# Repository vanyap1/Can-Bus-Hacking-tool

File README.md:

# Can bus tools

For this moment the tool is not ready to use. 
This is only old first draft version.

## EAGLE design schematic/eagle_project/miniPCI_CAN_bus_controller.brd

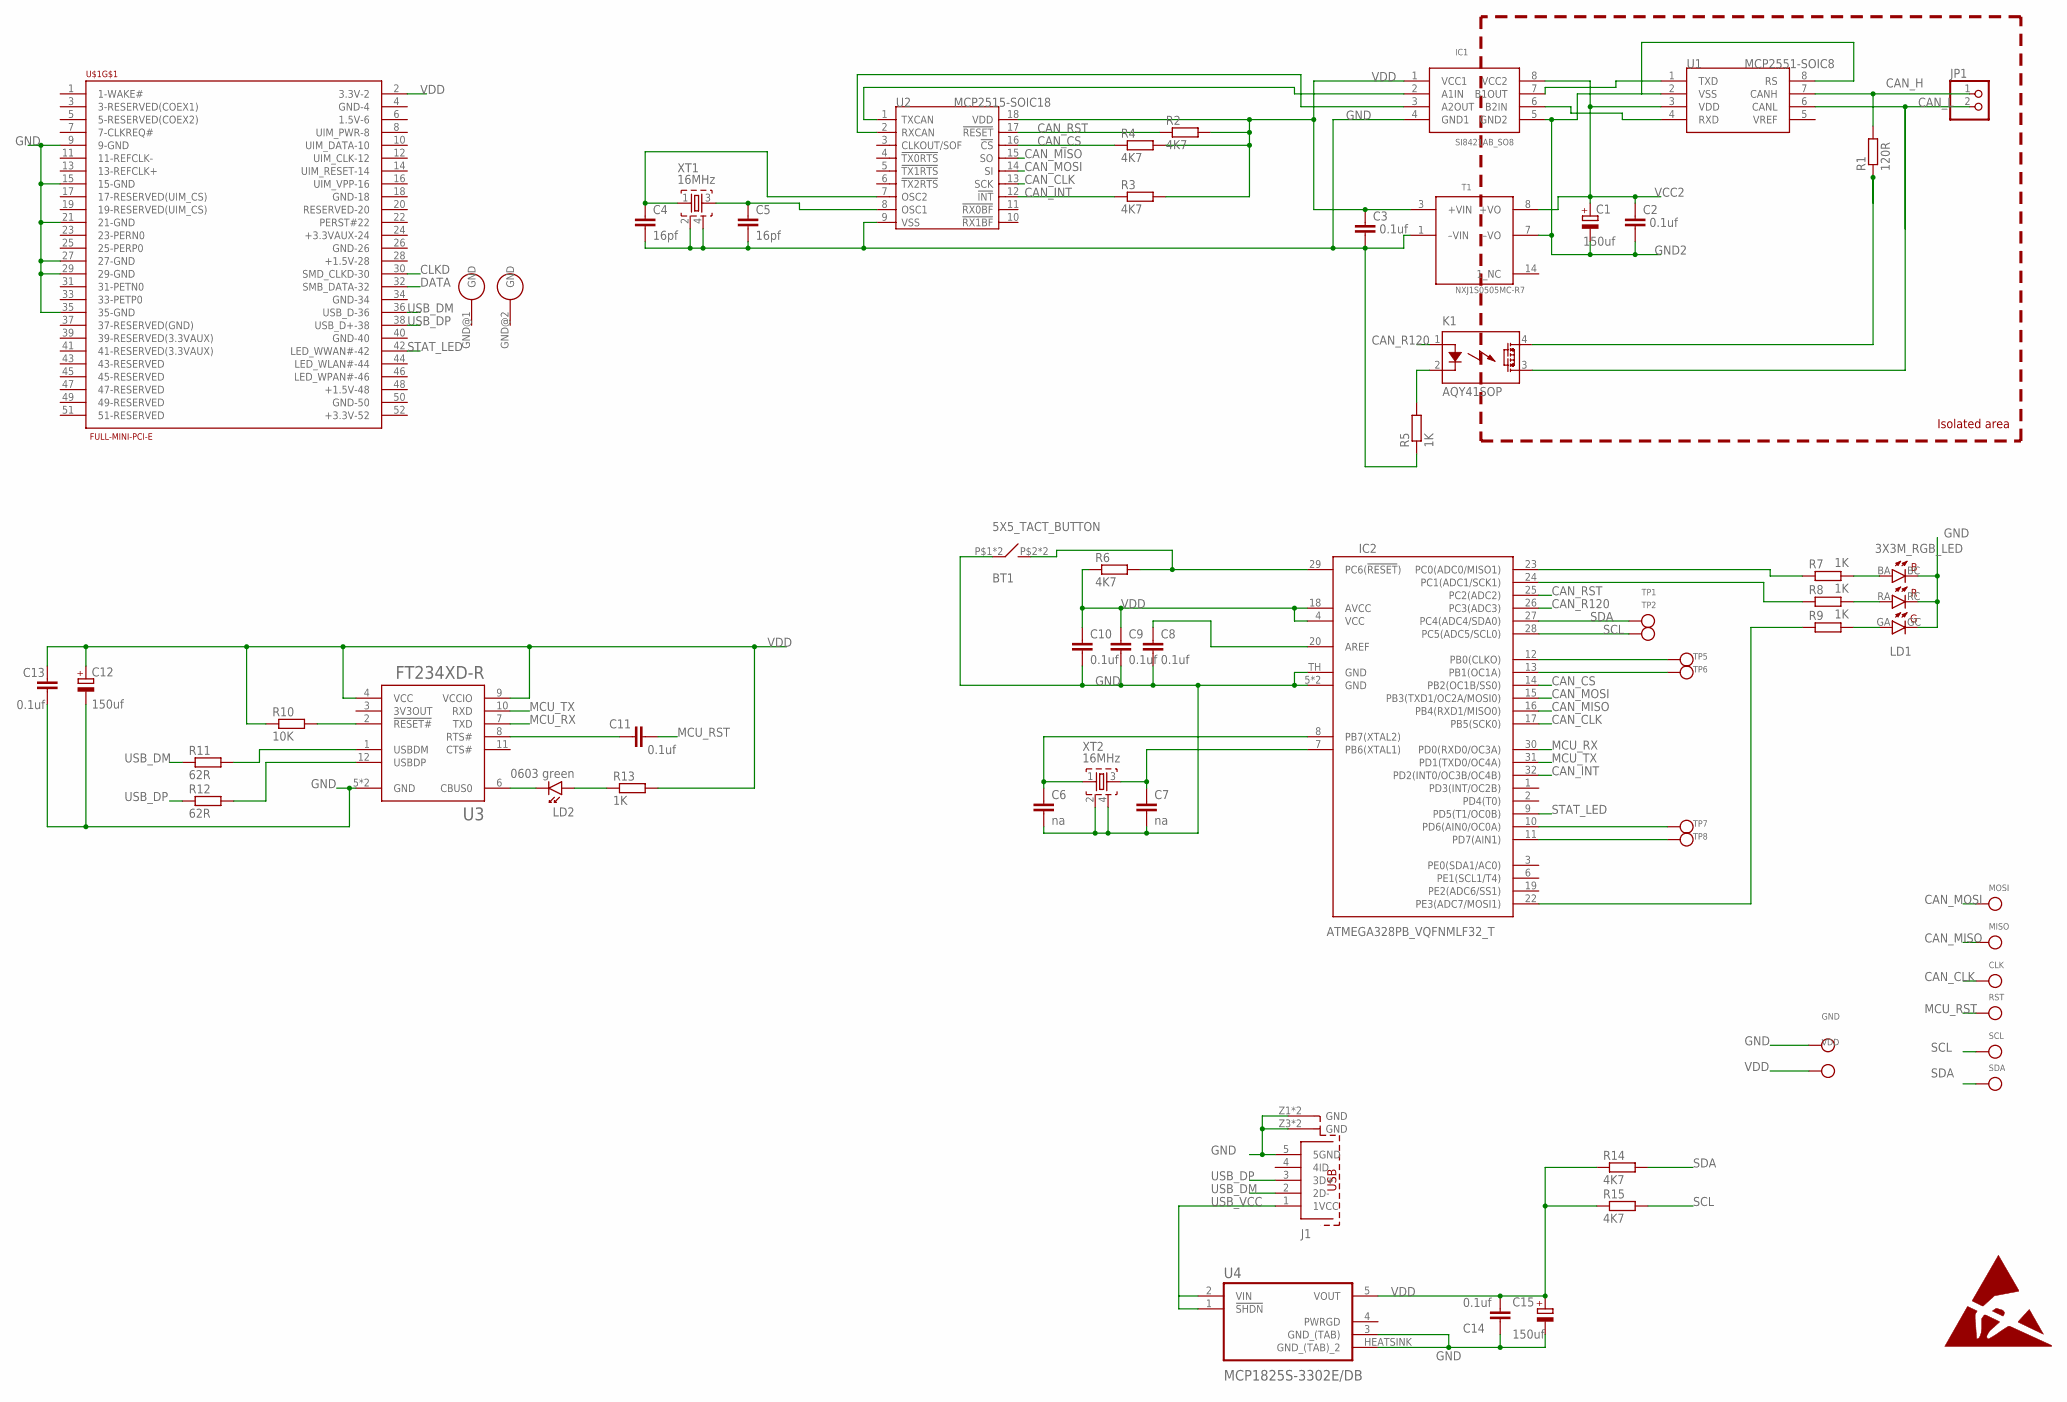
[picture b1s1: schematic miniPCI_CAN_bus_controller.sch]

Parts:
BT1: 5X5_TACT_BUTTON; 5X5MM_SMD_CY
C1, C12, C15: 150uf; KA-3528ASYC
C2, C3, C8, C9, C10, C11, C13, C14: 0.1uf; 0603
C4, C5: 16pf; 0603
C6, C7: na; 0603
CLK: TEST_POINT_D2MM; TP
GND: TEST_POINT_D2MM; TP
IC1: SI8421AB_SO8; SO8
IC2: ATMEGA328PB_VQFNMLF32_T; MLF32-TH
J1: MINI_USB_TYP_B_@; 65100516121
JP1: PINHD-1X2; 1X02
K1: AQY41SOP; SOP04
LD1: 3X3M_RGB_LED; 3X3MRGB_LED
LD2: 0603 green; 0603_P
MISO: TEST_POINT_D2MM; TP
MOSI: TEST_POINT_D2MM; TP
R1: 120R; 0603
R2, R3, R4, R6, R14, R15: 4K7; 0603
R5, R7, R8, R9, R13: 1K; 0603
R10: 10K; 0603
R11, R12: 62R; 0603
RST: TEST_POINT_D2MM; TP
SCL: TEST_POINT_D2MM; TP
SDA: TEST_POINT_D2MM; TP
T1: NXJ1S0505MC-R7; NXJ1SXXXXMC
TP1, TP2, TP5, TP6, TP7, TP8: TEST_POINT_D2MM; TP
U1: MCP2551-SOIC8; SO8
U2: MCP2515-SOIC18; SO18L
U3: FT234XD-R; IC_FT234XD-R
U4: MCP1825S-3302E/DB; SOT230P700X180-4N
U$1: FULL-MINI-PCI-E
VDD: TEST_POINT_D2MM; TP
XT1, XT2: 16MHz; QUARTZ_3X3MM

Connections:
CAN_CLK: CLK.P$1, IC2.17 (PB5(SCK0)), U2.13 (SCK)
CAN_CS: IC2.14 (PB2(OC1B/SS0)), R4.1, U2.16 (!CS)
CAN_H: JP1.1, R1.2, U1.7 (CANH)
CAN_INT: IC2.32 (PD2(INT0/OC3B/OC4B)), R3.1, U2.12 (!INT)
CAN_L: JP1.2, K1.3 (DS2), U1.6 (CANL)
CAN_MISO: IC2.16 (PB4(RXD1/MISO0)), MISO.P$1, U2.15 (SO)
CAN_MOSI: IC2.15 (PB3(TXD1/OC2A/MOSI0)), MOSI.P$1, U2.14 (SI)
CAN_R120: IC2.26 (PC3(ADC3)), K1.1 (A)
CAN_RST: IC2.25 (PC2(ADC2)), R2.1, U2.17 (!RESET)
CLKD: U$1.30 (SMD_CLKD-30)
DATA: U$1.32 (SMB_DATA-32)
GND: BT1.P$1 (1), BT1.P$4 (1), C3.2, C4.2, C5.2, C6.2, C7.2, C8.2, C9.2, C10.2, C12.M (-), C13.1, C14.1, C15.M (-), GND.P$1, IC1.4 (GND1), IC2.5 (GND), IC2.21 (GND), IC2.TH (GND), J1.5 (5GND), J1.Z1 (GND), J1.Z2 (GND), J1.Z3 (GND), J1.Z4 (GND), LD1.BC, LD1.GC, LD1.RC, R5.1, T1.1 (–VIN), U2.9 (VSS), U3.5 (GND), U3.13 (GND), U4.3 (GND_(TAB)), U4.HEATSINK (GND_(TAB)_2), U$1.9 (9-GND), U$1.15 (15-GND), U$1.21 (21-GND), U$1.27 (27-GND), U$1.29 (29-GND), U$1.35 (35-GND), U$1.GND@1 (GND), U$1.GND@2 (GND), XT1.2, XT1.4, XT2.2, XT2.4
GND2: C1.M (-), C2.2, IC1.5 (GND2), T1.7 (–VO), U1.2 (VSS), U1.8 (RS)
MCU_RST: BT1.P$2 (4), BT1.P$3 (4), C11.2, IC2.29 (PC6(!RESET!)), R6.2, RST.P$1
MCU_RX: IC2.30 (PD0(RXD0/OC3A)), U3.7 (TXD)
MCU_TX: IC2.31 (PD1(TXD0/OC4A)), U3.10 (RXD)
unnamed: R11.2, U3.1 (USBDM)
unnamed: K1.4 (DS1), R1.1
unnamed: IC1.2 (A1IN), U2.1 (TXCAN)
unnamed: IC1.7 (B1OUT), U1.1 (TXD)
unnamed: IC1.6 (B2IN), U1.4 (RXD)
unnamed: IC1.3 (A2OUT), U2.2 (RXCAN)
unnamed: C8.1, IC2.20 (AREF)
unnamed: LD2.1 (K), U3.6 (CBUS0)
unnamed: LD2.2 (A), R13.1
unnamed: C6.1, IC2.8 (PB7(XTAL2)), XT2.1
unnamed: C4.1, U2.7 (OSC2), XT1.1
unnamed: C5.1, U2.8 (OSC1), XT1.3
unnamed: K1.2 (K), R5.2
unnamed: C7.1, IC2.7 (PB6(XTAL1)), XT2.3
unnamed: LD1.BA, R7.2
unnamed: LD1.RA, R8.2
unnamed: LD1.GA, R9.2
unnamed: R12.2, U3.12 (USBDP)
unnamed: IC2.23 (PC0(ADC0/MISO1)), R7.1
unnamed: IC2.24 (PC1(ADC1/SCK1)), R8.1
unnamed: IC2.22 (PE3(ADC7/MOSI1)), R9.1
unnamed: IC2.10 (PD6(AIN0/OC0A)), TP7.P$1
unnamed: IC2.11 (PD7(AIN1)), TP8.P$1
unnamed: C11.1, U3.8 (RTS#)
unnamed: IC2.13 (PB1(OC1A)), TP6.P$1
unnamed: IC2.12 (PB0(CLKO)), TP5.P$1
unnamed: R10.2, U3.2 (!RESET#)
SCL: IC2.28 (PC5(ADC5/SCL0)), R15.2, SCL.P$1, TP2.P$1
SDA: IC2.27 (PC4(ADC4/SDA0)), R14.2, SDA.P$1, TP1.P$1
STAT_LED: IC2.9 (PD5(T1/OC0B)), U$1.42 (LED_WWAN#-42)
USB_DM: J1.2 (2D-), R11.1, U$1.36 (USB_D-36)
USB_DP: J1.3 (3D+), R12.1, U$1.38 (USB_D+-38)
USB_VCC: J1.1 (1VCC), U4.1 (!SHDN), U4.2 (VIN)
VCC2: C1.P (+), C2.1, IC1.8 (VCC2), T1.8 (+VO), U1.3 (VDD)
VDD: C3.1, C9.1, C10.1, C12.P (+), C13.2, C14.2, C15.P (+), IC1.1 (VCC1), IC2.4 (VCC), IC2.18 (AVCC), R2.2, R3.2, R4.2, R6.1, R10.1, R13.2, R14.1, R15.1, T1.3 (+VIN), U2.18 (VDD), U3.4 (VCC), U3.9 (VCCIO), U4.5 (VOUT), U$1.2 (3.3V-2), VDD.P$1

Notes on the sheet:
Isolated area

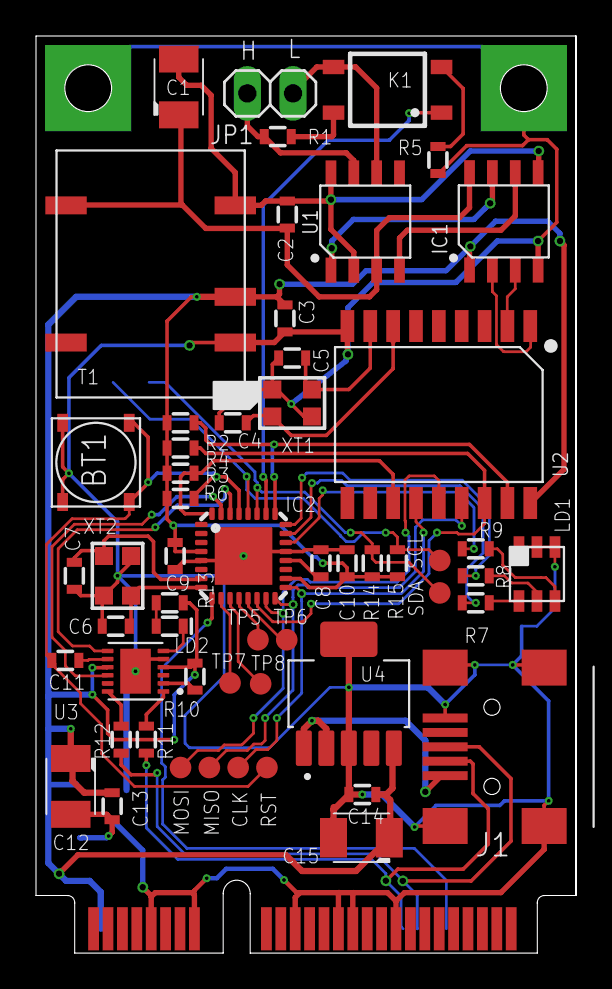
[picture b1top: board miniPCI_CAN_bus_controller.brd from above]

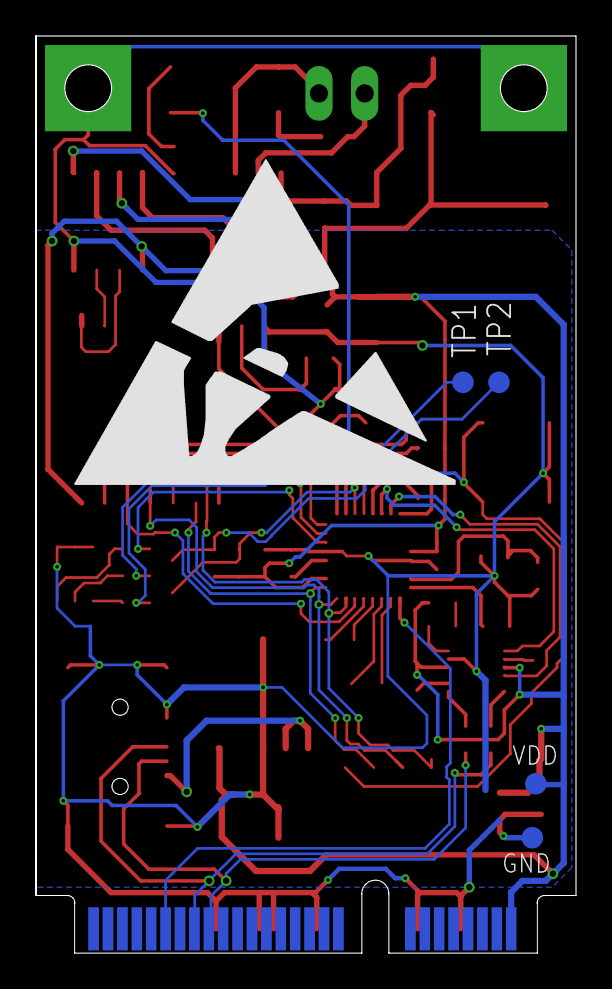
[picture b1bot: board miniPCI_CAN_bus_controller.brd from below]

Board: 2 copper layers, 30.0 x 51.0 mm, 61 parts (5 on the bottom side), 49 nets.

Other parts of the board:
U$2: ESD

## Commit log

2023-07-13 created new project
